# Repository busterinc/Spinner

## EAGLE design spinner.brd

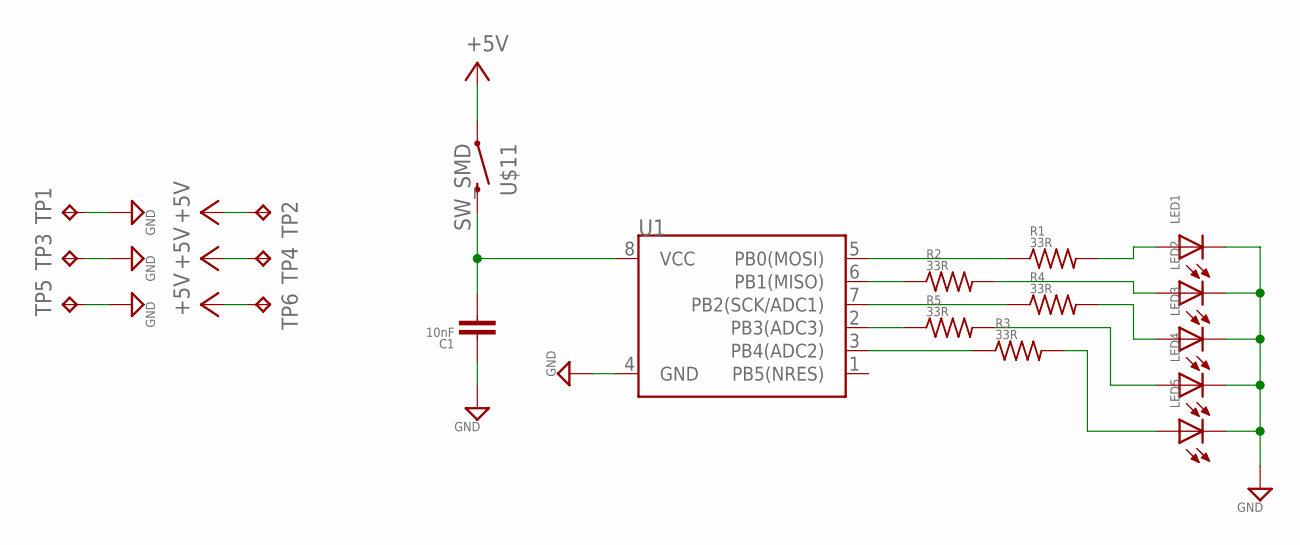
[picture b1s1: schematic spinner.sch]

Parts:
C1: 10nF; 0603
LED1, LED2, LED3, LED4, LED5: LEDC; 0603LED
R1, R2, R3, R4, R5: 33R; 0603
TP1, TP2, TP3, TP4, TP5, TP6: TPB1,27; B1,27
U1: Tiny85-20-SMT; SO08-EIAJ
U$11: SW_SMD

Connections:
+5V: TP2.TP, TP4.TP, TP6.TP, U$11.1
GND: C1.1, LED1.K (C), LED2.K (C), LED3.K (C), LED4.K (C), LED5.K (C), TP1.TP, TP3.TP, TP5.TP, U1.4 (GND)
unnamed: R1.1, U1.5 (PB0(MOSI))
unnamed: R2.1, U1.6 (PB1(MISO))
unnamed: R3.1, U1.3 (PB4(ADC2))
unnamed: R5.1, U1.2 (PB3(ADC3))
unnamed: LED1.A, R1.2
unnamed: LED2.A, R2.2
unnamed: LED3.A, R4.2
unnamed: LED4.A, R5.2
unnamed: LED5.A, R3.2
unnamed: R4.1, U1.7 (PB2(SCK/ADC1))
unnamed: C1.2, U1.8 (VCC), U$11.2

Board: 2 copper layers, 19 parts (0 on the bottom side), 13 nets, no tracks yet.

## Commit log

2020-01-16 Primer commit, se trabajó schematic, falta reemplazar librerías externas.

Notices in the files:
parts and their libraries:
SparkFun-DigitalIC: Licensing: Creative Commons ShareAlike 4.0 International - https://creativecommons.org/licenses/by-sa/4.0
